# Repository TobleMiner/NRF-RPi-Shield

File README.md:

Raspberry Pi NRF Shield
=======================

Small and simple Shield for NRF24 wireless modules. Supports several SMD and non-SMD NRF24 footprints.

Backside provides footprints for installation of additional smoothing capacitors (please install at least one 100 nF capacitor, a lot of NRF modules become really unstable without one) and a 3.3 V regulator for use with high current draw NRF modules with builtin power amplifiers.

Goes well together with https://github.com/TobleMiner/kernelstuff/tree/master/modules/nrf24l01

PCB top

PCB bottom

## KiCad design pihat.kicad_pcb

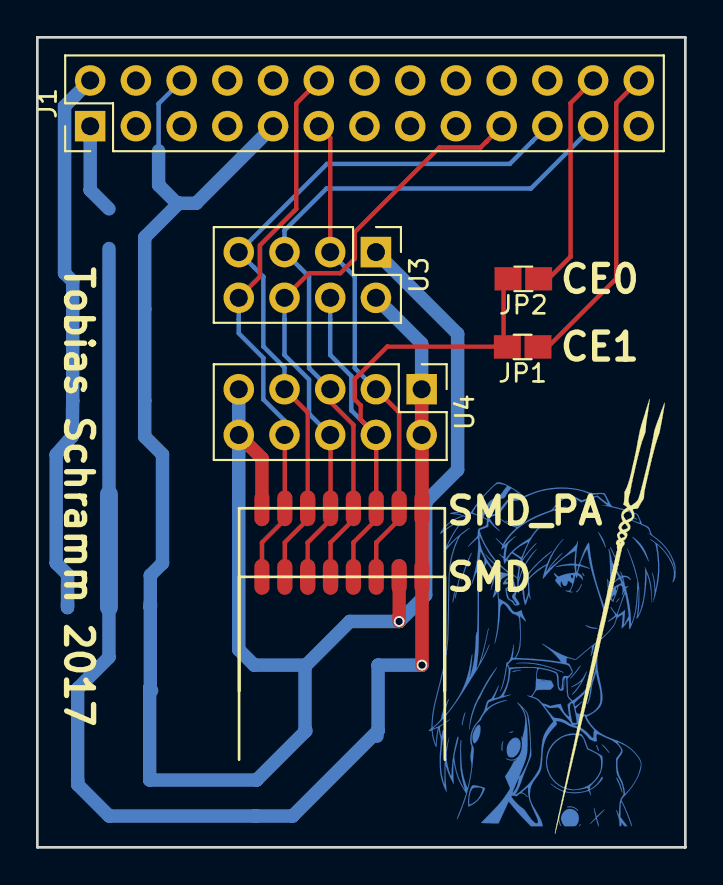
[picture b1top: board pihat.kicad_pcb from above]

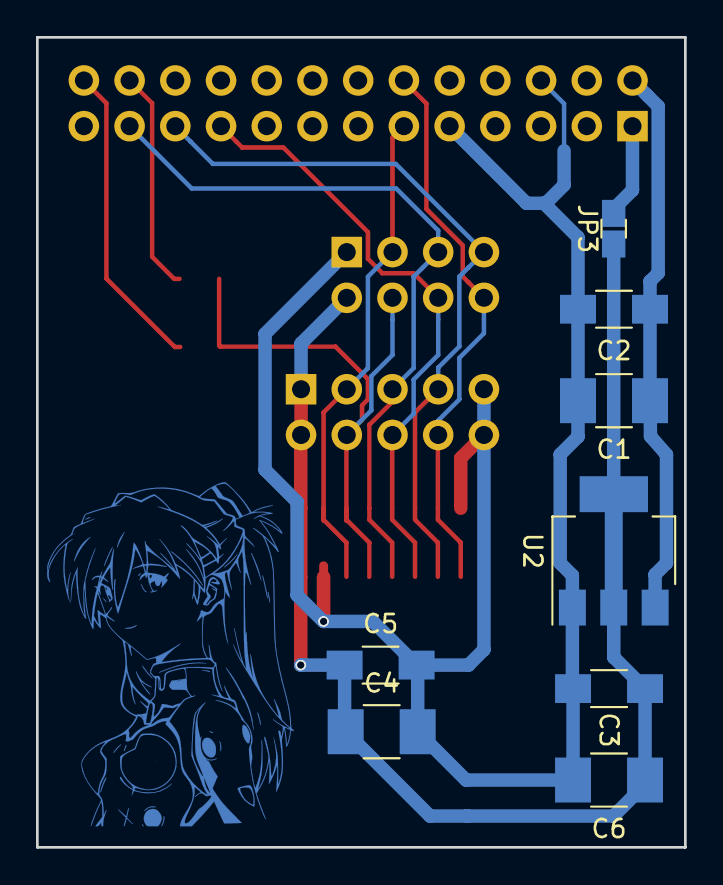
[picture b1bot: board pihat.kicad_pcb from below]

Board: 2 copper layers, 36.0 x 45.0 mm, 15 parts (8 on the bottom side), 12 nets.

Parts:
C1, C4, C6: 100µ; C_1210_HandSoldering
C2, C3, C5: 100n; C_1206_HandSoldering
J1: CONN_02X13; Pin_Header_Straight_2x13_Pitch2.54mm
JP1, JP2, JP3: Jumper_NO_Small; J_0603
U2: LM1117-3.3; SOT-223-3Lead_TabPin2
U3: nRF24L01+; Pin_Header_Straight_2x04_Pitch2.54mm
U4: nRF24L01+_10pin; Pin_Header_Straight_2x05_Pitch2.54mm
U5: nRF24L01P_SMD; nrf24l01_smd
U6: nRF24L01P_SMD_PA; nrf24l01_smd

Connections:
+3V3: C3.1, C4.1, C5.1, C6.1, JP3.1, U2.2, U3.2, U4.1, U4.2, U5.1, U6.1
+5V: C1.1, C2.1, J1.2, U2.3
/CE: J1.11, U3.3, U4.3, U5.3, U6.2
/CSN: JP1.2, JP2.2, U3.4, U4.4, U5.4, U6.3
/IRQ: J1.12, U3.8, U4.8, U5.8, U6.7
/MISO: J1.21, U3.7, U4.7, U5.7, U6.6
/MOSI: J1.19, U3.6, U4.6, U5.6, U6.5
/SCK: J1.23, U3.5, U4.5, U5.5, U6.4
GND: C1.2, C2.2, C3.2, C4.2, C5.2, C6.2, J1.6, J1.9, U2.1, U3.1, U4.9, U4.10, U5.2, U6.8
unnamed: J1.1, JP3.2
unnamed: J1.24, JP2.1
unnamed: J1.26, JP1.1

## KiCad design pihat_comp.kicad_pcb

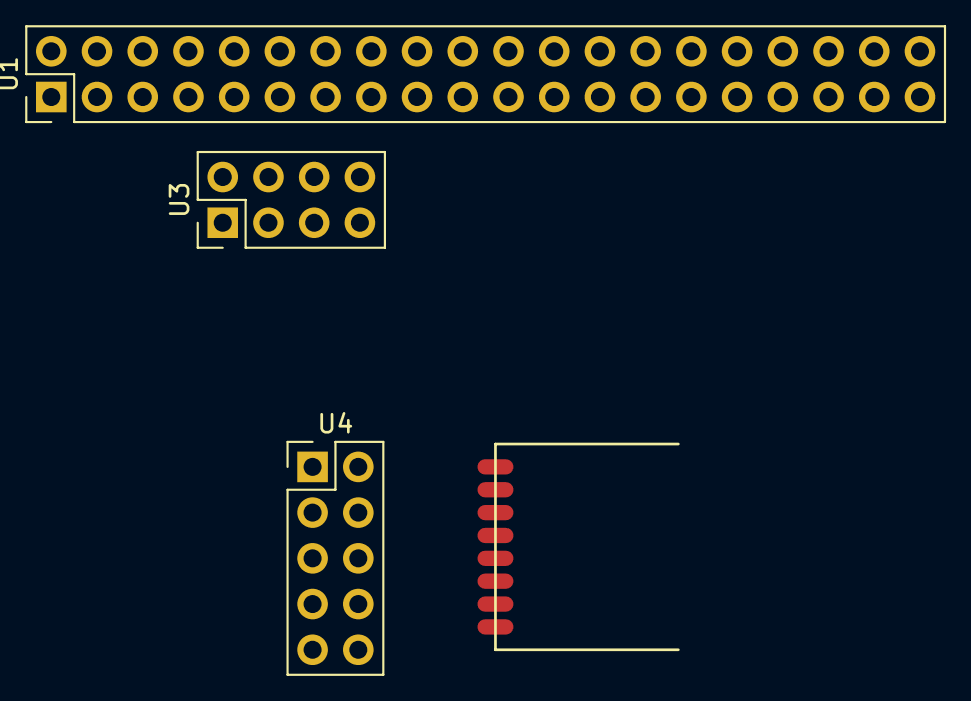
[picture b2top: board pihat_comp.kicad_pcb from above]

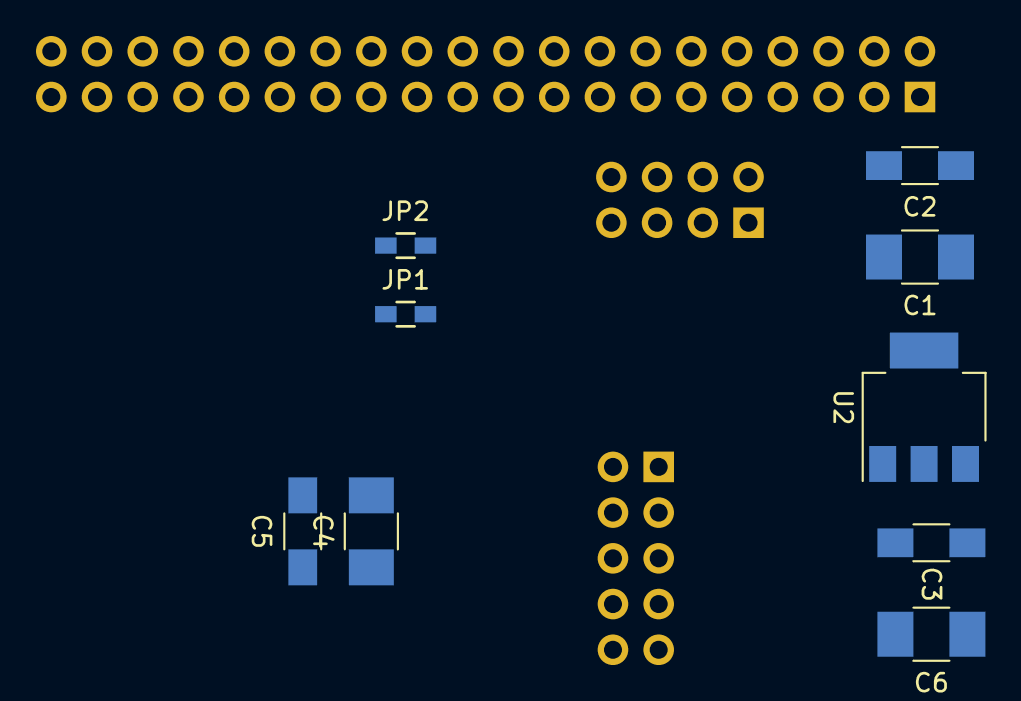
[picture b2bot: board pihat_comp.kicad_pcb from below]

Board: 2 copper layers, 13 parts (9 on the bottom side), 11 nets, no tracks yet.

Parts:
C1, C4, C6: 100µ; C_1210_HandSoldering
C2, C3, C5: 100n; C_1206_HandSoldering
JP1, JP2: Jumper_NO_Small; R_0603_HandSoldering
U1: Raspberry_Pi_2_3; Pin_Header_Straight_2x20_Pitch2.54mm
U2: LM1117-3.3; SOT-223-3Lead_TabPin2
U3: nRF24L01+; Pin_Header_Straight_2x04_Pitch2.54mm
U4: nRF24L01+_10pin; Pin_Header_Straight_2x05_Pitch2.54mm
U5: nRF24L01P_SMD; nrf24l01_smd

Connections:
+3V3: C3.1, C4.1, C5.1, C6.1, U1.1, U2.2, U3.2, U4.1, U5.1
+5V: C1.1, C2.1, U1.2, U2.3
/CE: U1.11, U3.3, U4.3, U5.3
/CSN: JP1.2, JP2.2, U3.4, U4.4, U5.4
/IRQ: U1.12, U3.8, U4.8, U5.8
/MISO: U1.21, U3.7, U4.7, U5.7
/MOSI: U1.19, U3.6, U4.6, U5.6
/SCK: U3.5, U4.5, U5.5
GND: C1.2, C2.2, C3.2, C4.2, C5.2, C6.2, U1.6, U2.1, U3.1, U4.9, U4.10, U5.2
unnamed: JP1.1, U1.26
unnamed: JP2.1, U1.24

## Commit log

2019-02-05 Add README
2019-02-05 Add pcb screenshots
2019-02-05 Make README more comprehensive
